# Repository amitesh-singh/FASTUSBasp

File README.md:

### FASTUSBasp programmer for AVR Microcontrollers

This is the fast ISP programmer for AVR MCUs based on cheap stm32f103c8t6 aka `blue-pill` board with usb-to-serial support.

### Release

- v1.0.0:  https://github.com/amitesh-singh/FASTUSBasp/releases/tag/v1.0.0

#### FastUSBASPv2 board

#### Perf board

### Correcting wrong pullup at USB D+

This blue pill board has wrong pullup resistor at usb D+ line.
You might need to fix it before using blue pill as an AVR programmer.
Refer to this guide: [http://amitesh-singh.github.io/stm32/2017/10/09/correcting-usbpullup-resistor.html][fixpullup-link]

### how to upload firmware

#### blue pill board with correct pullup at USB D+ line
 Download the binaries from https://github.com/amitesh-singh/FASTUSBasp/releases/tag/v1.0.0

If you have fixed the pullup at D+ line, use `fastusbasp.bin`
The pre-compiled binary is at `fastusbasp.bin`.

```shell
$ st-flash write fastusbasp.bin 0x08000000
```

#### blue pill board with wrong pullup at USB D+ line
In case, you did not fix the wrong pullup at D+ line, use
`fastusbasp-wrongpullup.bin` binary instead

```shell
$ st-flash write fastusbasp-wrongpullup.bin 0x08000000
```

### How to use

#### ISP connections

It uses SPI2 to communicate to AVR.

Blue pill | AVR
--------- | -------
PB15  |   MOSI
PB14  |   MISO
PB13  |   SCK
PA8   |   RST
5v or 3.3v |     5v
GND        |    GND

#### Serial connections
Serial ports are `PA10`(RX) and `PA9` (TX).
This can be used to debug AVR Microcontrollers.

Blue pill | AVR
--------- | -------
PA10      | TX
PA9       | RX

All pins SPI2(PB15, PB14, PB13), Serial(PA10, PA9) and RST(PA8) used are 5V tolerant.

#### udev rule

Refer to [udev/README.md](udev/README.md)

### On plugging to PC
#### Linux
When you plug this device to PC, you should get following message on`dmesg -wH`

```shell
[Jan20 13:31] usb 3-1.1: new full-speed USB device number 5 using xhci_hcd
[  +0.107774] usb 3-1.1: New USB device found, idVendor=16c0, idProduct=05dc
[  +0.000004] usb 3-1.1: New USB device strings: Mfr=1, Product=2, SerialNumber=3
[  +0.000002] usb 3-1.1: Product: fastusbasp
[  +0.000002] usb 3-1.1: Manufacturer: http://amitesh-singh.github.io
[  +0.000001] usb 3-1.1: SerialNumber: AARAV
[  +0.040797] cdc_acm 3-1.1:1.0: ttyACM0: USB ACM device
[  +0.000804] usbcore: registered new interface driver cdc_acm
[  +0.000000] cdc_acm: USB Abstract Control Model driver for USB modems and ISDN adapters
```

`/dev/ttyACM0` is the serial port.

#### Windows
- Download Zadig (https://zadig.akeo.ie/)
- Insert device to USB. Wait until windows can't install it.
- Launch Zadig
- Select in Zadig our device from ComboBox
- Select driver Type libusbK
- Press Install Driver
- Wait until Zadig is done with installing driver and that results into Windows to detect the device.

### Probe AVR

```shell
$ avrdude -c usbasp-clone -p m16

avrdude: AVR device initialized and ready to accept instructions

Reading | ################################################## | 100% 0.00s

avrdude: Device signature = 0x1e9403 (probably m16)

avrdude: safemode: Fuses OK (E:FF, H:D8, L:CF)

avrdude done.  Thank you.
```

### Upload program to AVR

```shell
$ avrdude -c usbasp-clone -p m16 -U flash:w:blink.hex

avrdude: AVR device initialized and ready to accept instructions

Reading | ################################################## | 100% 0.00s

avrdude: Device signature = 0x1e9403 (probably m16)
avrdude: NOTE: "flash" memory has been specified, an erase cycle will be performed
         To disable this feature, specify the -D option.
avrdude: erasing chip
avrdude: reading input file "blink.hex"
avrdude: input file blink.hex auto detected as Intel Hex
avrdude: writing flash (150 bytes):

Writing | ################################################## | 100% 0.02s

avrdude: 150 bytes of flash written
avrdude: verifying flash memory against blink.hex:
avrdude: load data flash data from input file blink.hex:
avrdude: input file blink.hex auto detected as Intel Hex
avrdude: input file blink.hex contains 150 bytes
avrdude: reading on-chip flash data:

Reading | ################################################## | 100% 0.01s

avrdude: verifying ...
avrdude: 150 bytes of flash verified

avrdude: safemode: Fuses OK (E:FF, H:D8, L:CF)

avrdude done.  Thank you.

```

### Read flash
```shell
$ avrdude -c usbasp-clone -p m16 -U flash:r:flash.bin:r

avrdude: AVR device initialized and ready to accept instructions

Reading | ################################################## | 100% 0.00s

avrdude: Device signature = 0x1e9403 (probably m16)
avrdude: reading flash memory:

Reading | ################################################## | 100% 0.33s

avrdude: writing output file "flash.bin"

avrdude: safemode: Fuses OK (E:FF, H:D8, L:CF)

avrdude done.  Thank you.

$ hexdump flash.bin
0000000 c029 0000 c02f 0000 c02d 0000 c02b 0000
0000010 c029 0000 c027 0000 c025 0000 c023 0000
0000020 c021 0000 c01f 0000 c01d 0000 c01b 0000
0000030 c019 0000 c017 0000 c015 0000 c013 0000
0000040 c011 0000 c00f 0000 c00d 0000 c00b 0000
0000050 c009 0000 2411 be1f e5cf e0d4 bfde bfcd
0000060 d002 c017 cfcd 9ab8 9ac0 ef2f ed83 e390
0000070 5021 4080 4090 f7e1 c000 0000 98c0 ef2f
0000080 ed83 e390 5021 4080 4090 f7e1 c000 0000
0000090 cfeb 94f8 cfff

```

### Flash Read/Write speed

Flash Write speed: 15 KBps
Flash Read Speed: 52.5 KBps

### Bit clock speed
`FASTUSBasp` starts out with a fast ISP clock frequency (default: 3 MHz),
   so the `-B bitclock` option might be required to achieve stable communication
in case target MCU `F_CPU` is bit low < 12MHz
#### Supported bitclock speed

- default (without -B): 3 MHz
- 1.5 MHz
- 750 KHz
- 375 KHz
- 187.5 KHz

### how to compile from source and upload the firmware
To build fastusbasp firmware from source code, follow below guidelines.

#### compile
Refer my post on how to setup stm32 devlopment environment on Arch linux.
http://amitesh-singh.github.io/stm32/2017/04/09/setting-stm32-dev-environment-arch-linux.html

Make sure you have compiled `libopencm3` library.

```shell
$ git clone --recurse-submodules https://github.com/amitesh-singh/FASTUSBasp
$ mkdir build
$ cd build
$ cmake ../
$ make
```
#### Upload the firmware
##### using STLINK
###### with st-flash
connect `st-link` programmer to `blue-pill` and upload the firmware

```shell
$ make fastusbasp-upload

```

###### with openocd

```shell
$ make fasusbasp-ocdupload

```

##### using serial port

Install `stm32flash` utility on linux.
To program `stm32f103` via USART, you need to set `BOOT0` as `1`
and leave `BOOT1` as `0`.

Connect any usb to uart converter device and connect PA9 to RXD and PA10 to TXD
and connect GND.

```shell
$ make fastusbasp-serialupload

```

### Links

- http://amitesh-singh.github.io/stm32/2017/05/21/FASTUSBasp-programmer-avr.html
- https://hackaday.io/project/21189-fastusbasp-programmer-for-avr

[fixpullup-link]: http://amitesh-singh.github.io/stm32/2017/10/09/correcting-usbpullup-resistor.html

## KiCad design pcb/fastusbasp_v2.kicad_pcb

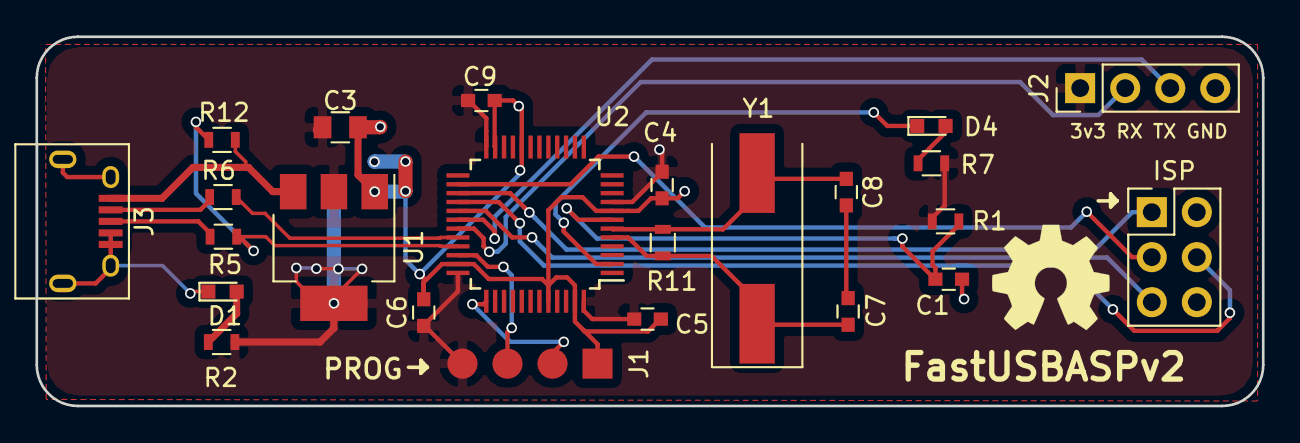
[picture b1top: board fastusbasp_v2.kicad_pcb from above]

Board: 2 copper layers, 69.2 x 20.8 mm, 24 parts (0 on the bottom side), 22 nets.

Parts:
C1: 100nF; C_0603
C3: 10uF; C_0805
C4, C5, C6, C9: 100nf; C_0603
C7, C8: 20pF; C_0603
D1, D4: LED; LED_0603
ISP: AVR-ISP-6; Pin_Header_Straight_2x03_Pitch2.54mm
J1: PROG; Pin_Header_SMD_pads_1x04_pitch2.54mm
J2: CONN_01X04; Pin_Header_Straight_1x04_Pitch2.54mm
J3: USB_OTG; USB_Micro-B
R1: 10k; R_0603
R2, R7: 1k; R_0603
R5, R6: 20R; R_0603
R11: 1M; R_0603
R12: 1.5k; R_0603
U1: LM1117-3.3; SOT-223-3_TabPin2
U2: STM32F103C8Tx; LQFP-48_7x7mm_Pitch0.5mm
Y1: 16MHz; Crystal_SMD_HC49-SD

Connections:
+3V3: C3.1, C4.1, C5.1, C6.1, C9.1, J1.4, J2.1, R1.1, R2.2, R7.2, U1.2, U2.9, U2.24, U2.36, U2.48
+5V: J3.1, R12.2, U1.3
/D_N: R6.1, U2.32
/D_P: R5.1, R12.1, U2.33
/ISP_MISO: ISP.1, U2.27
/ISP_MOSI: ISP.4, U2.28
/ISP_RESET: ISP.5, U2.29
/ISP_SCK: ISP.3, U2.26
/PGM_LED: D4.1, U2.2
/RESET: C1.1, R1.2, U2.7
/RXD: J2.2, U2.31
/SWCLK: J1.2, U2.37
/SWDIO: J1.3, U2.34
/TXD: J2.3, U2.30
GND: C1.2, C3.2, C4.2, C5.2, C6.2, C9.2, D1.1, ISP.6, J1.1, J2.4, J3.4, J3.5, J3.6, U1.1, U2.8, U2.20, U2.23, U2.35, U2.44, U2.47
unnamed: C7.1, R11.1, U2.5, Y1.1
unnamed: C7.2, C8.2
unnamed: C8.1, R11.2, U2.6, Y1.2
unnamed: D1.2, R2.1
unnamed: D4.2, R7.1
unnamed: J3.2, R6.2
unnamed: J3.3, R5.2

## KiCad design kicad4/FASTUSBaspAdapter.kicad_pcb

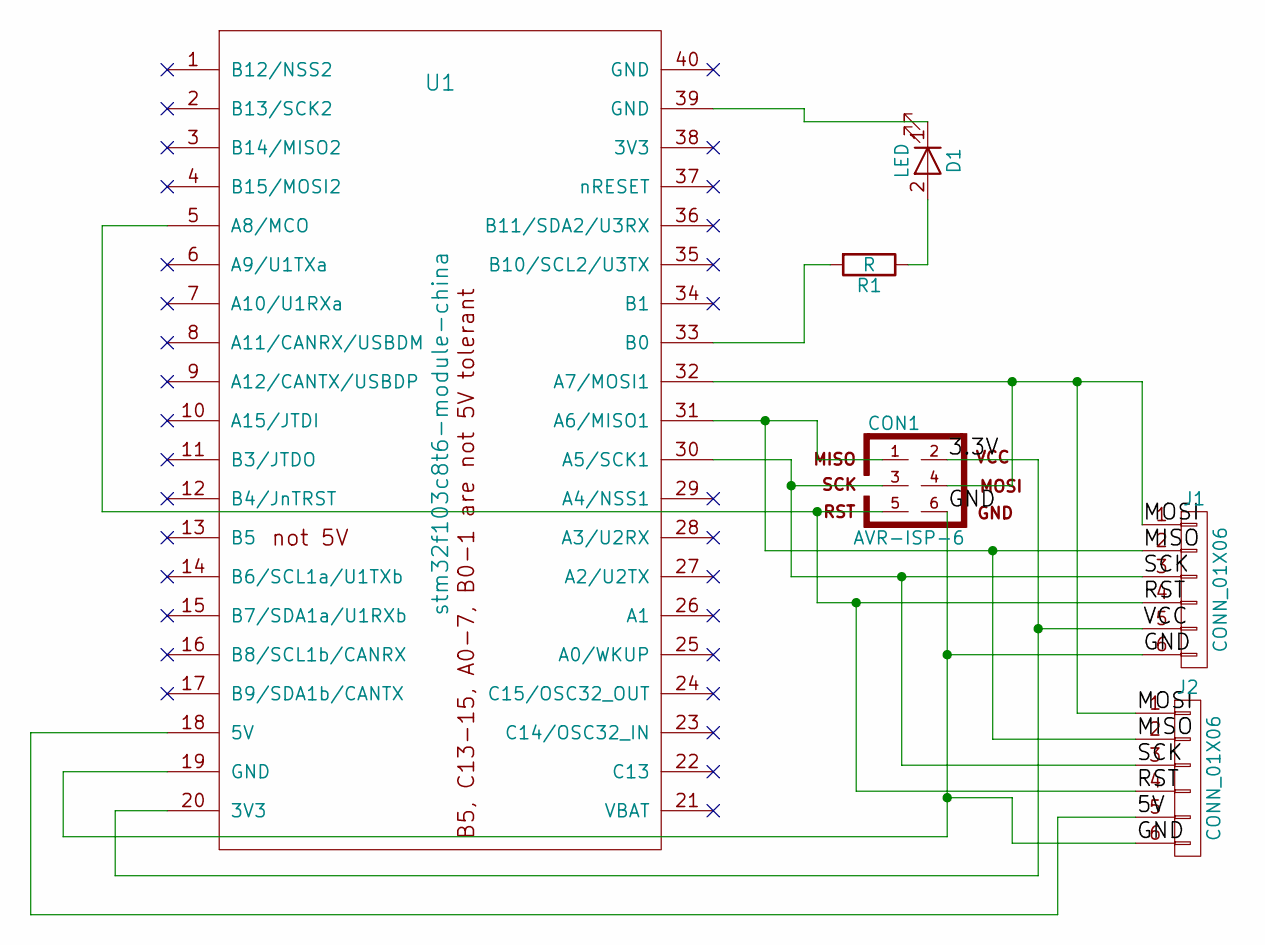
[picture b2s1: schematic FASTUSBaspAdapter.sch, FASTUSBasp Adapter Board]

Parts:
CON1: AVR-ISP-6; Pin_Header_Straight_2x03_Pitch2.54mm
D1: LED; LED_0805_HandSoldering
J1, J2: CONN_01X06; Pin_Header_Straight_1x06_Pitch2.00mm
R1: R; R_0805_HandSoldering
U1: stm32f103c8t6-module-china

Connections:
/3.3V: CON1.2, J1.5, U1.20 (3V3)
/5V: J2.5, U1.18 (5V)
/GND: CON1.6, J1.6, J2.6, U1.19 (GND)
/MISO: CON1.1, J1.2, J2.2, U1.31 (A6/MISO1)
/MOSI: CON1.4, J1.1, J2.1, U1.32 (A7/MOSI1)
/RST: CON1.5, J1.4, J2.4, U1.5 (A8/MCO)
/SCK: CON1.3, J1.3, J2.3, U1.30 (A5/SCK1)
unnamed: D1.1 (K), U1.39 (GND)
unnamed: D1.2 (A), R1.1
unnamed: R1.2, U1.33 (B0)

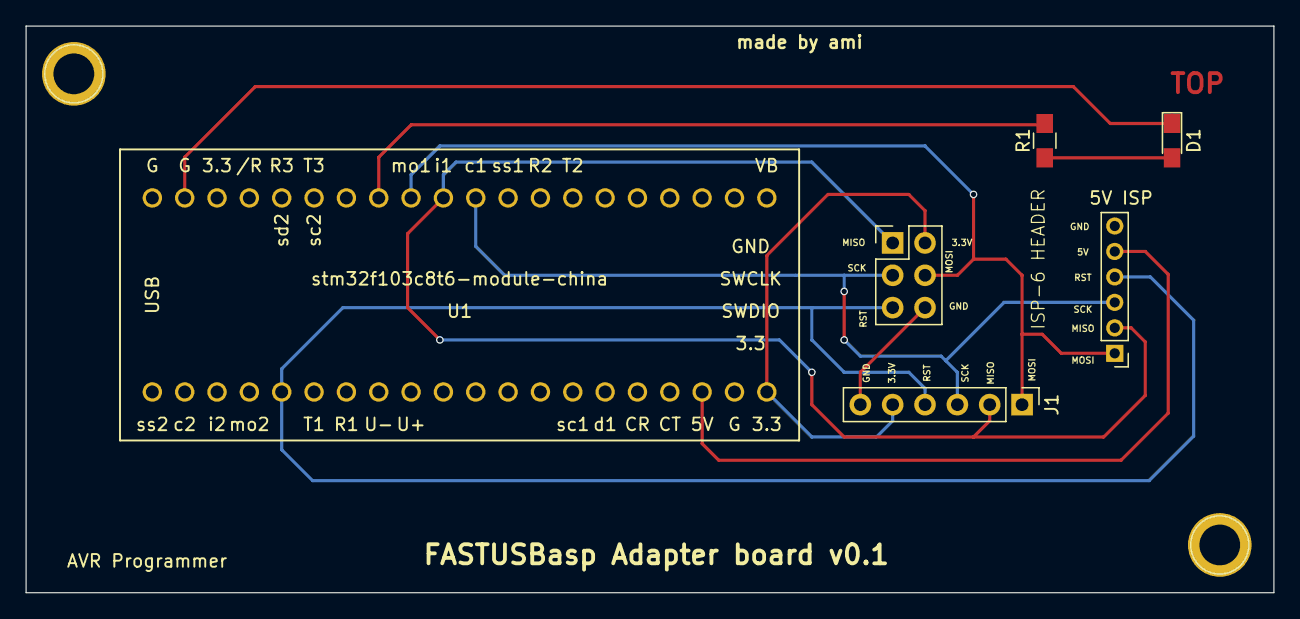
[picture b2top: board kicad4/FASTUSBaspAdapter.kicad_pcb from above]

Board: 2 copper layers, 98.0 x 44.5 mm, 6 parts (0 on the bottom side), 10 nets.

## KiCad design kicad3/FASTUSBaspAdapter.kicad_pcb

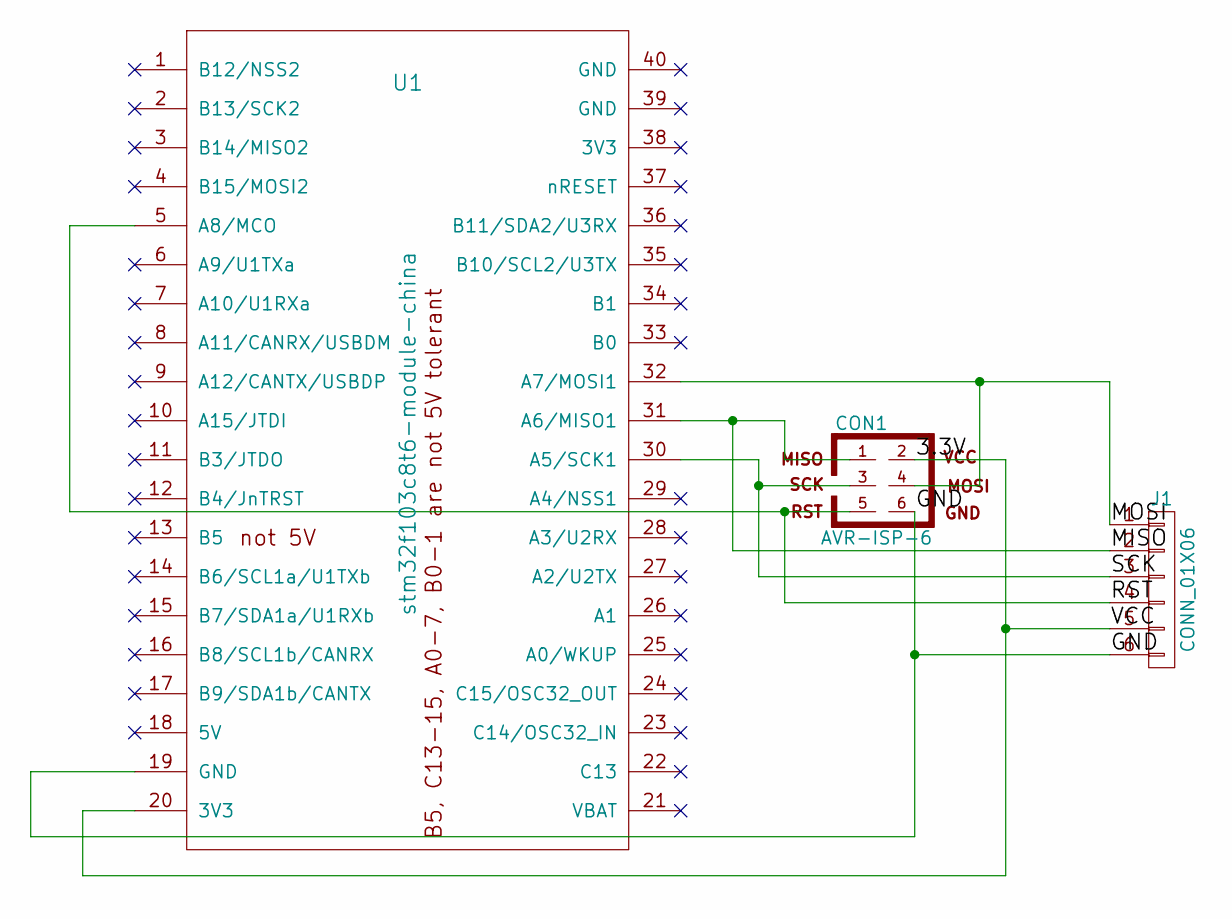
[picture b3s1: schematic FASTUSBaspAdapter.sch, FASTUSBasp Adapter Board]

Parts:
CON1: AVR-ISP-6; Pin_Header_Straight_2x03_Pitch2.54mm
J1: CONN_01X06; Pin_Header_Straight_1x06_Pitch2.00mm
U1: stm32f103c8t6-module-china

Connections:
/3.3V: CON1.2, J1.5, U1.20 (3V3)
/GND: CON1.6, J1.6, U1.19 (GND)
/MISO: CON1.1, J1.2, U1.31 (A6/MISO1)
/MOSI: CON1.4, J1.1, U1.32 (A7/MOSI1)
/RST: CON1.5, J1.4, U1.5 (A8/MCO)
/SCK: CON1.3, J1.3, U1.30 (A5/SCK1)

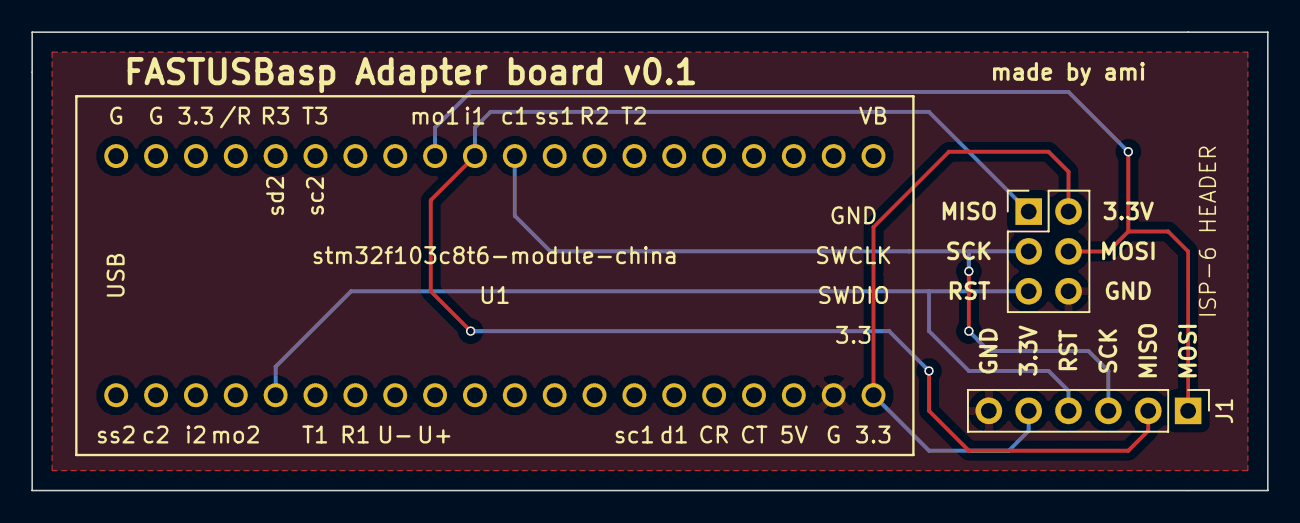
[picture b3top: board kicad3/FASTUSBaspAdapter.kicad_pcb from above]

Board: 2 copper layers, 78.7 x 29.2 mm, 3 parts (0 on the bottom side), 6 nets.

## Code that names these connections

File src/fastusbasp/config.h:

#ifndef _CONFIG_H
#define _CONFIG_H

#define ISP_BUS SPI2
#define ISP_BUS_RCC RCC_SPI2

#define ISP_RCC RCC_GPIOB
#define ISP_PORT GPIOB
#define ISP_MOSI GPIO15
#define ISP_MISO GPIO14
#define ISP_SCK  GPIO13

#define ISP_RST_RCC RCC_GPIOA
#define ISP_RST_PORT GPIOA
#define ISP_RST GPIO8

//define this to 1, if blue pill has wrong pull up at USB D+ line
#define USBDPLUS_WRONG_PULLUP 0

#endif

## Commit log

2017-04-15 Add code for FASTUSBasp
2017-04-15 sleep: fix the bug
    the timer is now synced with 48MHz F_CPU clock
2017-04-16 Add kicad schematics
2017-04-16 Add gerber files
2017-04-16 Add page settings into schematic & pcb
2017-04-16 Add schematic & board png image
    sabor wanted it :)
2017-04-16 improve the design little bit
2017-04-16 Add kicad with standard 6 pin isp header
    Thanks to sabor for the idea.
2017-04-17 Add modified gerber files
2017-04-17 Add panelize pcb
2017-04-18 Add better panilzed version 0.2
2017-04-22 Add copyright
2017-05-21 Add kicad3 files
2017-05-21 Add panelized rotate in 4 in 1 example
2017-05-23 update LICENSE
2017-05-27 Add debug ifdef around USART header file inclusion
2017-06-16 Add the components lib
2017-08-07 Add support of openocd
    This trick is based on video https://www.youtube.com/watch?v=0eHpoPZvI3U
    at nuttX channel.
    This allows you to flash the board upto 128Kb size
    which is pretty cool.
2017-08-07 Add new kicad designed
2017-08-08 cmake: disable stripping of efl file so that we can debug it via openocd
    stripping an elf file does not effect on bin size which we upload
    to MCU
2017-08-08 Move TODOs
2017-08-08 update IMAGE
2017-08-14 create a header file for macro definitions
2017-08-14 tpi: add initial code.
2017-08-14 not sure if it works
2017-08-14 Add config.h in Cmakefile.
2017-08-15 Add perfboard photo into README.md
2017-08-15 show the board at top
2017-08-18 Add support of serial upload using usb to uart converter.
2017-08-28 Add support of hse8mhz_out_48Mhz clock
    Earlier we were using hsi_out_48Mhz which has
    clock tolerance upto 1% which is higher than usb clock tolerance
    12.0+-0.03 Mb/s ~ 0.25
    Although i did not face any problems yet.
    Also HSI is temperature sensitive so its better to use HSE instead.
    libopencm3 does not have this function so write one and add it.
2017-08-28 correct prescalar values
2017-09-18 Add fastusbap firmware binary
2017-10-02 Add Gitter badge
2017-10-03 Add fastusbasp udev rules
2017-10-03 Revert "Add a Gitter chat badge to README.md"
2017-10-03 Add gitter.im badge
2017-10-09 use correct pullup code to avoid usb connection issues
    well, it works almost 90% of the time with usbdplus hack..
    but its better to have code for correct pullup code.
2017-10-09 Add firmware binary
2017-10-09 Add abt how to fix usb d+ pullup Resistor
2017-10-09 website link is more preferable than hackaday page.
2017-10-10 comment out not required code and add comments abt usb software hack in main.c
2017-10-10 Add abt udev rules in README
2017-10-10 update udev README
2017-12-15 Add macro for spi bus and clock.
2017-12-15 Add binary for wrong pullup
2017-12-15 update the binary
2017-12-15 Add SPI2 instead
    Since SPI1 is not 5V tolerant so its better to use
    SPI2 instead which is 5V tolerant.
2017-12-15 clocks: define all used clocks in one go at the begining.
2017-12-15 make spi2 work
    fix some typos and its better to use 2MHZ_OUTPUT
2017-12-15 Use SPI2 to communicate instead
    Since SPI1 is not 5V tolerant so its better to use
    SPI2 instead which is 5V tolerant.
    Also define all used clocks in one go at the begining.
2017-12-15 update fastusbasp binary - now it uses spi2 for communication.
2017-12-15 Add fastusbasp-wrongpullup binary - it uses spi2 now.
2017-12-15 update README abt SPI2
2017-12-15 remove udev rules folder
    we don't need this anymore.
2017-12-19 change the directory heirarchy.
2018-01-13 Bugfix: Flashing of ATMega1284p does not work
2018-01-14 update the binary after the fix.
2018-01-20 remove kicad.
    the kicad files are old and does not reperesent correct pinout diagram
2018-01-20 Add Fastusbasp version 2 code.
2018-01-20 move license at the top of file.
2018-01-20 LICENSE: Add tavish name
2018-01-21 firmware: serial tx: fix the bug
    update the firmware binary as well.
2018-01-21 serial: move LICENSE at top
2018-01-25 firmware: implement 48Mhz clock and use it.
    Running clock at 48Mhz gives lower and stable SPI speed.
    The spi slave clock in AVR is F_CPU/4 (for spi master, its F/2)
    so a typical atmega328p running at 16Mhz can do 16/4 = 4 Mhz spi speed
    at max. Lets respect that.
    default: 48/16 = 3Mhz
    48/32 = 1.5Mhz and so on.
2018-01-25 fix the typo
2018-01-25 update binary
2018-01-27 add pcb files
2018-01-27 add new render
2018-02-01 fix typo in README.md
2018-02-08 fix the cdc structure.
2018-02-19 Set theme jekyll-theme-modernist
2018-03-03 fix the compilation
    Make it compilable with latest libocm3 code.
    the control ep cb signature is changed.
2018-03-11 fix udev readme file.
2018-04-30 disable rst, mosi & SS on isp disconnect.
    should fix https://github.com/amitesh-singh/FASTUSBasp/issues/5
2018-06-03 cmake: fix linking error.
    It seems that libocm3 has changed the ld files location.
2018-12-17 fix the meson build with new libocm3
    location of ld file is changed.
2019-01-10 correct the ld file.
2019-01-13 this fixes the warnings while linking
    redeclaration of rom/ram warnings error.
2020-05-26 Fixed Composite Device Error on Windows OS
2020-05-27 Forget change endpoint number on init
2020-05-27 Add baudrate set from terminal. Tuned query polling
2020-05-29 Add documentation for windows
2020-05-30 make function static.
2020-05-30 update binaries
    - supports windows OS
    - serial support is better!
2021-02-08 use rcc_clock_setup_pll(&rcc_hse_configs[RCC_CLOCK_HSE8_72MHZ]);
    instead of rcc_clock_setup_in_hse_8mhz_out_72mhz();
2021-06-13 queue: reimplement it
2021-06-13 fix the compilation erorr.
    ref #6
2022-02-11 Add buymecoffee logo
2022-02-11 update TODOs.
2023-08-17 fix(spi): remove spi_reset()
    libocm3 has removed this function
2023-12-21 fix a typo
2023-12-21 Add workflow and add libopencm3 as submodule
2025-01-03 bump up libopencm3 to latest master
2025-01-03 fix ocdupload
2025-09-07 fix a typo
    use ISP_BUS instead of hardcoded SPI1
    Thanks to Alexander Inyukhin for reporting
2025-09-07 bump up libopencm3
